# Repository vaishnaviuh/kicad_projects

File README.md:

# kicad_projects

My PCB designs in KiCad 10.

## USB charger boards (`USB/charge/`)

Two 4-layer boards that take **12–24 V DC in** and give **5 V USB charging out**,
using a TI **LMR33630ADDA** buck regulator.

| Board | Folder | Output |
|---|---|---|
| USB-A charger | [`USB/charge/USB-A/`](USB/charge/USB-A/) | 5 V, USB-A port (BC1.2 dedicated charging port) |
| USB-C charger | [`USB/charge/USB_C/`](USB/charge/USB_C/) | 5 V, USB-C port (Rp advertisement + BC1.2) |

**Protection chain:** PPTC fuse → Bourns thermal cutoff → reverse-polarity Schottky →
input TVS, plus a TVS on the 5 V rail and USBLC6 ESD protection on D+/D−.

- Design review notes and open items: [`USB/charge/README.md`](USB/charge/README.md)
- Thermal cutoff selection: [`USB/charge/USB-A/TCO_README.md`](USB/charge/USB-A/TCO_README.md)

## Tools

| Script | What it does |
|---|---|
| `USB/charge/tools/fab-export.py` | Exports BOM, pick-and-place, Gerbers and drill files into `fab_output/` |
| `USB/tools/kicad-strip-fills.py` | Git filter that strips zone fills from `.kicad_pcb` files |
| `USB/tools/setup-git-filters.sh` | Turns that filter on for your clone |

## Opening the boards

1. Install [KiCad 10](https://www.kicad.org/).
2. Open `USB_A.kicad_pro` or `USB_C.kicad_pro`.
3. In the PCB editor, press **B** (Fill All Zones) before exporting anything.

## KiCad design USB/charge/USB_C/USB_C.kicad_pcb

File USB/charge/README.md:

# USB Charger Boards — Design Check & Fab Outputs

Two KiCad projects, both 12–24V DC in → 5V USB charging out:

| Project | Output | Regulator | Status of review |
|---|---|---|---|
| `USB-A/` | 5V / 2.1A, USB-A port (BC1.2 DCP) | TI LMR33630ADDA | **Reviewed — findings below** |
| `USB_C/` | 5V, USB-C port (Rp advertisement + BC1.2 DCP) | TI LMR33630ADDA | **Reviewed — findings below** |

## Goal

Go through each board thoroughly, one at a time, before production:
ERC/ERC-parity, DRC, schematic/netlist sanity, current paths and copper
sizing, protection chain, and fab-output freshness. USB-A first, then USB-C.

## Tooling notes (apply to both projects)

- **Zone fills are stripped from commits** by the `kicadfills` clean filter
  (`USB/tools/kicad-strip-fills.py`). The filter must be enabled per
  clone: run `USB/tools/setup-git-filters.sh` once, otherwise every
  KiCad save shows thousands of `filled_polygon` diff lines. (This was
  missing in this clone and has been enabled now.)
- A fresh checkout therefore has **empty pours** — run Fill All Zones (`B`)
  in pcbnew (or the headless equivalent) before exporting anything.
- **`tools/fab-export.py`** exports BOM, pick-and-place,
  4-layer Gerbers + Excellon drill, and a timestamped zip for **both**
  projects into `<project>/fab_output/`. It refuses to run on unfilled
  boards. These schematics have no MPN field, so the BOM groups by
  Value + Footprint.

## USB-A review findings (2026-07-29)

### Checks run

ERC, DRC with zone refill and schematic parity (KiCad 10.0.5 CLI), full
netlist trace, per-net copper measurement on the board file, gerber content
check against the current layout.

### Critical — fix before fabrication

1. **VBUS trace is far too thin for 2.1A.** The 5V path after the ferrite
   bead (FB1 pad 1 → J2 pin 1) runs ~19mm of **0.2mm-wide** track on F.Cu.
   At 2.1A that is roughly 45–50mΩ → ~100mV drop and substantial self-heating
   (IPC-2221 wants ~1mm+ at this current for a modest temperature rise).
   `VOUT_5V` before the bead has a dedicated In2.Cu plane — the problem is
   only the post-FB1 stretch. Widen to ≥1mm and/or pour a VBUS polygon.
2. **FB1 is an unspecified generic 0603 ferrite bead sitting in the full
   2.1A path.** Many 0603 beads are rated 1–2A with ~100mΩ DCR; combined
   with finding 1 the port voltage can fall below the USB minimum of 4.75V
   at full load. Specify a part rated ≥3A with low DCR (tens of mΩ), or
   move to a larger package.

### Should fix

3. **Input current path is all 0.2mm track**: J1 → F1 (4.4mm) → TCO1
   (9.9mm) → D3 (17.1mm) → `VIN_P` (~23mm). Carries up to ~1.1A at 12V
   input. Electrically marginal-OK, but the resistive heating sits right
   next to TCO1, whose trip point is the subject of the open thermal
   validation — widen these to keep the thermal test honest.
4. **DRC: 3 starved-thermal errors** (1 spoke instead of min 2) on GND pads
   of CH1, CI1 (input HF decoupling) and CV1 (VCC cap). Nudge parts or
   adjust the zone so the pads get proper relief — or solid connections,
   which are preferable for decoupling anyway.
5. **ERC: 3 "power input pin not driven" errors** (U1 VIN, J2 VBUS, one
   power symbol). Connectivity is real (verified in netlist); add
   `PWR_FLAG` symbols to silence them so real regressions stay visible.
6. **Test-point net-name parity warnings** (TP1/TP2): labels
   `Net-(F1-Pad2)` / `Net-(D3-A)` exist only on one pin each and mismatch
   the board's net names (`/…` prefix). Rename to meaningful labels (e.g.
   `VIN_FUSED`, `VIN_TCO`) and re-sync the PCB.

### Verified good

- **Regulation:** FB divider 100k/24.9k → 5.016V nominal (LMR33630 1.0V
  ref). EN divider 715k/100k → converter enables at ~10V input (UVLO
  sensible for a 12–24V spec).
- **Buck support parts** match the LMR33630 datasheet application:
  2×4.7µF + 220nF input, 4×22µF output, 100nF boot, 1µF VCC, 8.2µH
  Würth WE-PDF (ripple ~1.2A p-p worst case at 24V in — acceptable;
  confirm saturation current ≥ ~3A when locking the part number).
- **Protection chain:** PPTC fuse → Bourns thermal cutoff → series SS34
  reverse-polarity Schottky → SMAJ28A input TVS; SMAJ6.0A on the 5V rail;
  USBLC6-2SC6 ESD on D+/D−. Sound arrangement.
- **DCP identification:** D+/D− joined through 100Ω (R_DCP1) — valid BC1.2
  dedicated-charging-port signature.
- **Layout fundamentals:** 4-layer stack with GND on F/In1/B and a 5V plane
  on In2; U1 exposed pad has 8×0.3mm thermal vias; 0 unconnected items after
  zone refill; USB-A shield tied to GND.
- **Gerbers are current:** inner layers included, and the copper matches the
  post-"L1 swap" layout (verified pad coordinates inside the gerber).
  Regenerated fresh with `tools/fab-export.py` anyway.

### Pre-existing open items (documented in `USB-A/TCO_README.md`)

- TCO1 = SA77SB0 is a **placeholder**; thermal validation in the real
  enclosure is required before locking the trip temperature.
- Exact part numbers to confirm at procurement: F1 (PPTC — must be rated for
  the 24V input, many 1812 PPTCs are 16V parts), L1, FB1 (see finding 2),
  LED colour for D4.

## 3A retarget — changes applied (2026-07-29)

The output target was raised to **5V / 3A**. The following was applied
directly to both projects (schematics + boards, verified by ERC/DRC):

- **USB-C CC advertisement fixed for 3A:** D_CCREF1 (zener) and R_CCREF1
  deleted; RC1/RC2 (now "10k 1%") pull CC1/CC2 straight to VOUT_5V — the
  spec-table 10k@5V = 3A signature. Board tracks retargeted and bridged;
  DRC 0 unconnected, parity clean.
- **Setpoint raised:** RFB1 24.9k → 24.3k on both boards → ~5.12V at the
  regulator, extra IR-drop budget at 3A (still <5.25V worst case).
- **USB-C L1: 15µH → 8.2µH** (aligned with USB-A; lower DCR at 3A; lock a
  part with Isat ≥ 4.5A, Irms ≥ 3.5A).
- **BOM values updated on both boards:** F1 "3A PPTC 30V" (2920), D3 "SS54"
  (SMC), FB1 "FerriteBead 4A 20mR" (1206).
- **Copper widened where the existing placement allows** (DRC-verified):
  input chain J1→F1→TCO1→D3 now mostly 0.6–1.0mm on both boards; VOUT_5V
  runs 0.5–0.8mm (plus the In2 plane, which carries most of it).

### Left for manual layout (placement is too tight for scripted edits)

1. **F1 / D3 / FB1 footprint upgrades** (1812→2920, SMA→SMC, 0603→1206):
   the bigger bodies collide with TP1/TP2/J1/TCO1 (F1), REN1/U1/D1 (D3) and
   L1/CO1/CO2 (FB1). Schematics carry the new footprints, so DRC's
   schematic-parity check flags exactly these three per board as the to-do.
   Alternatives if space stays tight: D3 in SMB (B340LB) and FB1 in 0805
   (TDK MPZ2012-class, 6A) are electrically adequate.
2. **VBUS remains thin** — the corridor from FB1 to the connector maxes out
   at 0.25–0.4mm (USB-A) / mostly 0.2mm (USB-C) between existing pads,
   tracks, and the board edge. For 3A this needs a real reroute: move the
   run away from the CO2/CO3 pad row, or drop to B.Cu with a pair of ≥0.6mm
   vias, or dedicate a VBUS pour. **This is the single most important
   remaining item.**
3. Starved-thermal spokes (3 on USB-A, 9 on USB-C) — unchanged, still open.
4. USB-A data-line signature: DCP short only guarantees ~1.5A draw; if the
   port should source its full capability to phones/tablets, add an Apple
   2.4A divider or an auto-signature IC (TPS2513-class). Type-A cannot
   advertise 3A regardless.
5. TCO thermal validation must now run at **3A / 15W** load (see
   `USB-A/TCO_README.md`); expect the trip variant to move up (SA82/SA85).

## USB-C review findings (2026-07-29)

Same core design as USB-A (LMR33630ADDA buck, identical protection chain and
divider values, L1 = 15µH here), so the shared verdicts above apply. Checks
run: ERC, DRC with zone refill + schematic parity (0 parity issues,
0 unconnected), netlist trace, per-net copper measurement.

### Critical — fix before fabrication

1. **CC pull-up value is not a valid USB-C combination.** CC1/CC2 each pull
   up through 10k (RC1/RC2) to a zener-derived 3.3V rail (BZX584C-3V3 biased
   ~3mA via R_CCREF1 560Ω from the 5V rail). The spec's Rp values are
   56k/22k/10k to 5V, or 36k/12k/**4.7k** to 3.3V — 10k to 3.3V is not in
   the table. Nominal vRd at the sink ≈ 1.11V, only ~0.1V below the 1.23V
   threshold where sinks read a **3A** advertisement; with resistor, zener,
   and Rd tolerances a sink can legitimately conclude 3A and overload this
   ~2A supply. Fix: change RC1/RC2 to **12k** (clean 1.5A advertisement), or
   drop the zener rail entirely and use 22k straight to VOUT_5V. (Per-pin
   separate Rp resistors are correctly present.)
2. **Same VBUS thin-trace problem as USB-A:** ~29mm of 0.2mm track
   (24.5mm F.Cu + 4.9mm B.Cu) between FB1 and the connector's four VBUS
   pins, no VBUS pour. Widen/pour as on USB-A.
3. **Same FB1 unspecified 0603 ferrite bead** in the full-load path.

### Should fix

4. **Input path all 0.2mm** (J1→F1→TCO1→D3→VIN_P, ~53mm total) — same as
   USB-A finding 3.
5. **DRC: 9 starved-thermal errors**, mostly the USB-C connector's GND pads
   (A1, B1, B12, shield — across F/In1/B zones) plus U1 pad 1. Connector
   ground return and shield deserve solid/multi-spoke connections.
6. **ERC: 3 off-grid endpoint warnings** around D_CCREF1 (wire stubs of
   0.013/0.04mm). Connectivity is currently intact, but off-grid ends are
   how nets silently break on the next edit — tidy them.
7. Same PWR_FLAG ERC nits as USB-A.

### Verified good

- All four VBUS pins (A4/A9/B4/B9) and all GND pins (A1/A12/B1/B12 + shell)
  are connected; D+/D− tied across both rows with the 100Ω BC1.2 DCP short;
  SBU1/SBU2 correctly left open; USBLC6-2SC6 ESD on the data pair.
- L1 = 15µH (this board's "inductor swap"): ripple
  ~0.66A p-p worst case — comfortable.
- Same 4-layer stack (GND on F/In1/B, 5V plane on In2), 0 unconnected items
  after refill, schematic/board parity clean.

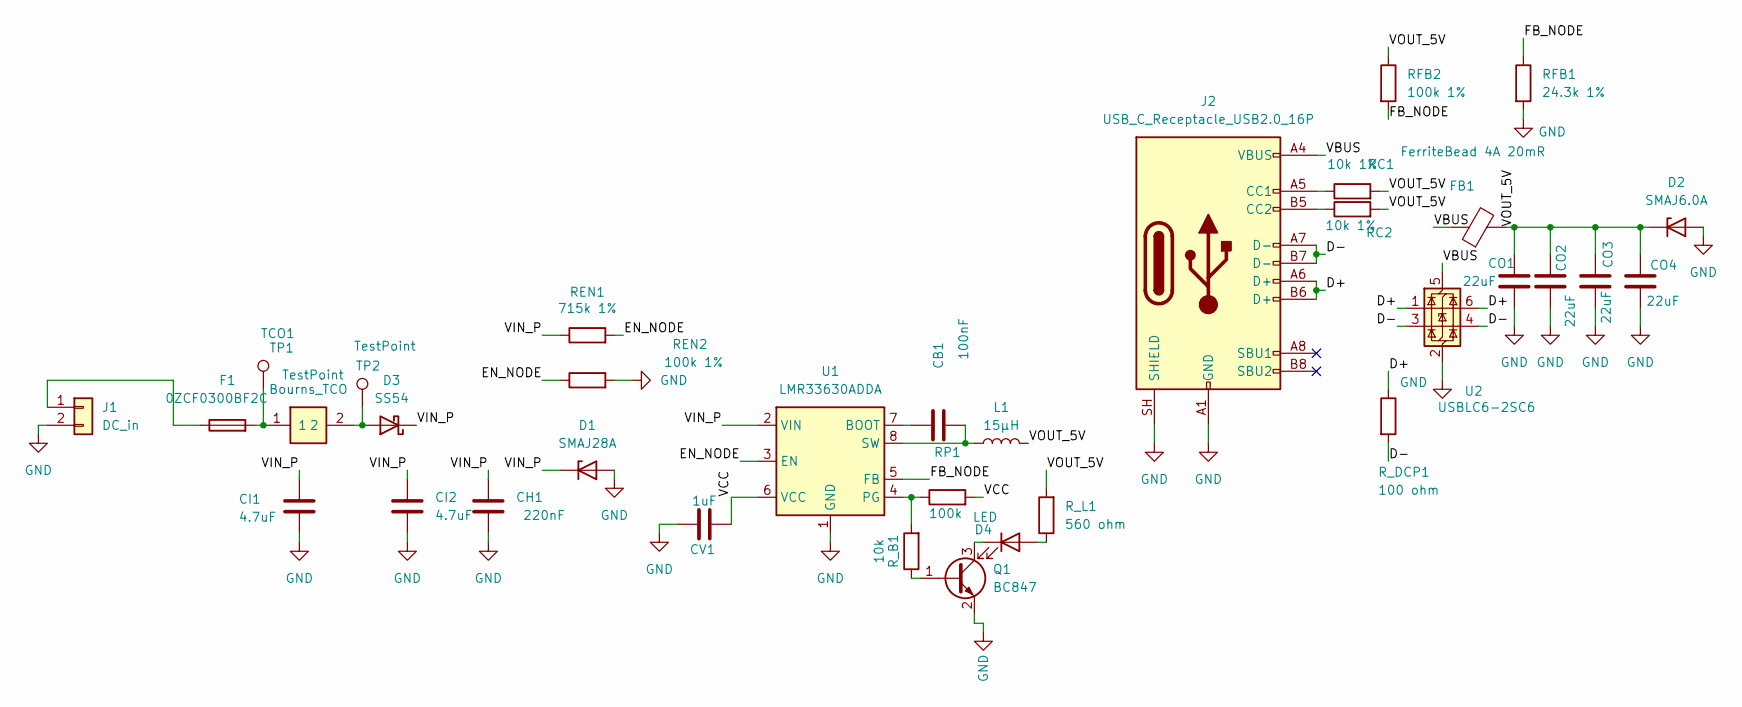
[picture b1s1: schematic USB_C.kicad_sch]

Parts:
CB1: 100nF; C_0603_1608Metric
CH1: 220nF; C_0603_1608Metric
CI1, CI2: 4.7uF; C_0805_2012Metric
CO1, CO2, CO3, CO4: 22uF; C_1210_3225Metric
CV1: 1uF; C_0603_1608Metric
D1: SMAJ28A; D_SMA
D2: SMAJ6.0A; D_SMA
D3: SS54; D_SMC
D4: LED; LED_0603_1608Metric
F1: 0ZCF0300BF2C; Fuse_2920_7451Metric
FB1: FerriteBead 4A 20mR; L_1206_3216Metric
J1: DC_in; TerminalBlock_Phoenix_PT-1,5-2-3.5-H_1x02_P3.50mm_Horizontal
J2: USB_C_Receptacle_USB2.0_16P; USB_C_Receptacle_GCT_USB4085
L1: 15µH; L_Wuerth_WE-PDF; MPN 744 779 815 1
Q1: BC847; SOT-23
RC1, RC2: 10k 1%; R_0603_1608Metric
REN1: 715k 1%; R_0603_1608Metric
REN2: 100k 1%; R_0603_1608Metric
RFB1: 24.3k 1%; R_0603_1608Metric
RFB2: 100k 1%; R_0603_1608Metric
RP1: 100k; R_0603_1608Metric
R_B1: 10k; R_0603_1608Metric
R_DCP1: 100 ohm; R_0603_1608Metric
R_L1: 560 ohm; R_0603_1608Metric
TCO1: Bourns_TCO
TP1, TP2: TestPoint; TestPoint_THTPad_D1.0mm_Drill0.5mm
U1: LMR33630ADDA; Texas_HSOP-8-1EP_3.9x4.9mm_P1.27mm_ThermalVias
U2: USBLC6-2SC6; SOT-23-6

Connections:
/D+: J2.A6 (D+), J2.B6 (D+), R_DCP1.1, U2.1 (I/O1), U2.6 (I/O1)
/D-: J2.A7 (D-), J2.B7 (D-), R_DCP1.2, U2.3 (I/O2), U2.4 (I/O2)
/EN_NODE: REN1.2, REN2.1, U1.3 (EN)
/FB_NODE: RFB1.1, RFB2.2, U1.5 (FB)
/VBUS: FB1.1, J2.A4 (VBUS), J2.A9 (VBUS), J2.B4 (VBUS), J2.B9 (VBUS), U2.5 (VBUS)
/VCC: CV1.2, RP1.2, U1.6 (VCC)
/VIN_P: CH1.1, CI1.1, CI2.1, D1.1 (K), D3.1 (K), REN1.1, U1.2 (VIN)
/VOUT_5V: CO1.1, CO2.1, CO3.1, CO4.1, D2.1 (K), FB1.2, L1.1, RC1.2, RC2.2, RFB2.1, R_L1.2
GND: CH1.2, CI1.2, CI2.2, CO1.2, CO2.2, CO3.2, CO4.2, CV1.1, D1.2 (A), D2.2 (A), J1.2, J2.A1 (GND), J2.A12 (GND), J2.B1 (GND), J2.B12 (GND), J2.SH (SHIELD), Q1.2 (E), REN2.2, RFB1.2, U1.1 (GND), U1.9 (GND), U2.2 (GND)
unnamed: D3.2 (A), TCO1.2, TP2.1 (1_1)
unnamed: D4.2 (A), R_L1.1
unnamed: D4.1 (K), Q1.3 (C)
unnamed: F1.2, TCO1.1, TP1.1 (1_1)
unnamed: F1.1, J1.1
unnamed: J2.A5 (CC1), RC1.1
unnamed: J2.B5 (CC2), RC2.1
unnamed: Q1.1 (B), R_B1.1
unnamed: CB1.2, U1.7 (BOOT)
unnamed: RP1.1, R_B1.2, U1.4 (PG)
unnamed: CB1.1, L1.2, U1.8 (SW)

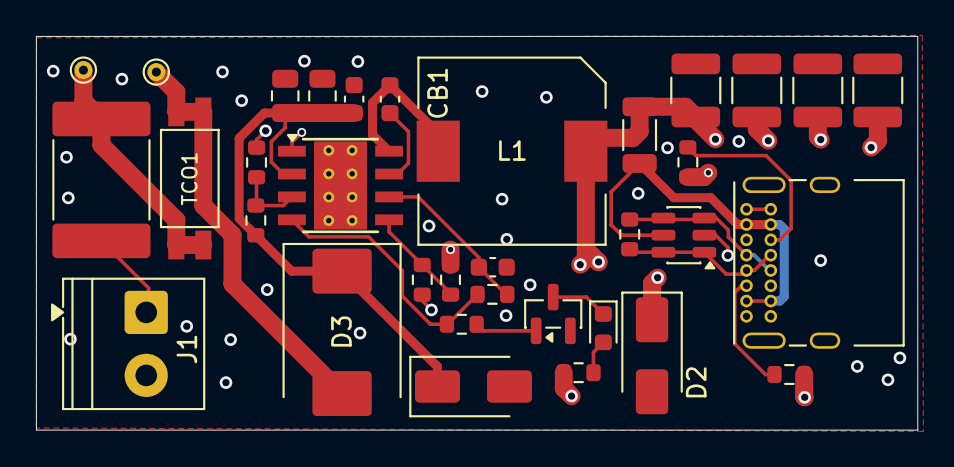
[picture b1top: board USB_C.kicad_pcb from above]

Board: 4 copper layers, 49.0 x 21.9 mm, 34 parts (0 on the bottom side), 20 nets.
